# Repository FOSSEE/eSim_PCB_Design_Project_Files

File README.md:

# ESP32-Based Silent SOS and Emergency Alert System

## 1. Project Overview

The Silent SOS is an ESP32-based emergency alert system designed to help users send emergency notifications when they are in a potentially dangerous situation.

The system uses an MPU6050 motion sensor to detect abnormal movement. When a possible emergency is detected, the system provides a 5-second cancellation period. If the user does not cancel the alert, an emergency notification is triggered.

The project uses Wi-Fi connectivity to send alerts through Firebase and Telegram.

## 2. Project Objectives

- Design a compact PCB for the Silent SOS system.
- Interface the MPU6050 motion sensor with the ESP32.
- Detect potential emergency situations using motion data.
- Provide a 5-second cancellation period before sending an alert.
- Send emergency notifications using Wi-Fi connectivity.

## 3. Hardware Components

| Component | Purpose |
|---|---|
| ESP32 DevKit V1 | Main microcontroller |
| MPU6050 | Motion and orientation detection |
| BC547 transistor | Switching circuit |
| Supporting components | Circuit interfacing and protection |

## 4. System Working

The system operates in three different states:

1. **SAFE:** Normal operating condition.
2. **ARMED:** Emergency detection is enabled.
3. **DANGER:** A potential emergency is detected.

### Emergency Alert Process

1. The MPU6050 continuously provides motion data.
2. The ESP32 processes the sensor readings.
3. When a potential emergency is detected, the system enters the DANGER state.
4. A 5-second cancellation period is provided.
5. If the alert is not cancelled, an emergency notification is sent through Firebase and Telegram.
6. The user's location is obtained through the connected smartphone's GPS.

## 5. PCB Design

The PCB is designed using **KiCad**.

The design integrates the ESP32 interface, motion sensor connections, and supporting electronic circuitry into a compact board.

### PCB Design Files

| File | Description |
|---|---|
| `SOS.kicad_pro` | KiCad project file |
| `SOS.kicad_sch` | Circuit schematic |
| `SOS.kicad_pcb` | PCB layout |
| `SOS.proj` | Supporting project file |

## 6. Software and Tools

- KiCad – Schematic and PCB design
- Arduino IDE – ESP32 programming
- Firebase – Emergency alert integration
- Telegram Bot API – Emergency notifications

## 7. Applications

- Personal emergency assistance
- Women's safety applications
- Emergency notification systems
- Personal safety monitoring

## 8. Project Repository

This repository contains the PCB design files and supporting documentation developed for the eSim Semester Long Internship – Autumn 2026, Submission Task 7.

## 9. Author

**Kaushik N.**  
Department of Electronics and Communication Engineering  
Chennai Institute of Technology

---

**Project:** ESP32-Based Silent SOS and Emergency Alert System  
**Internship:** eSim Semester Long Internship – Autumn 2026

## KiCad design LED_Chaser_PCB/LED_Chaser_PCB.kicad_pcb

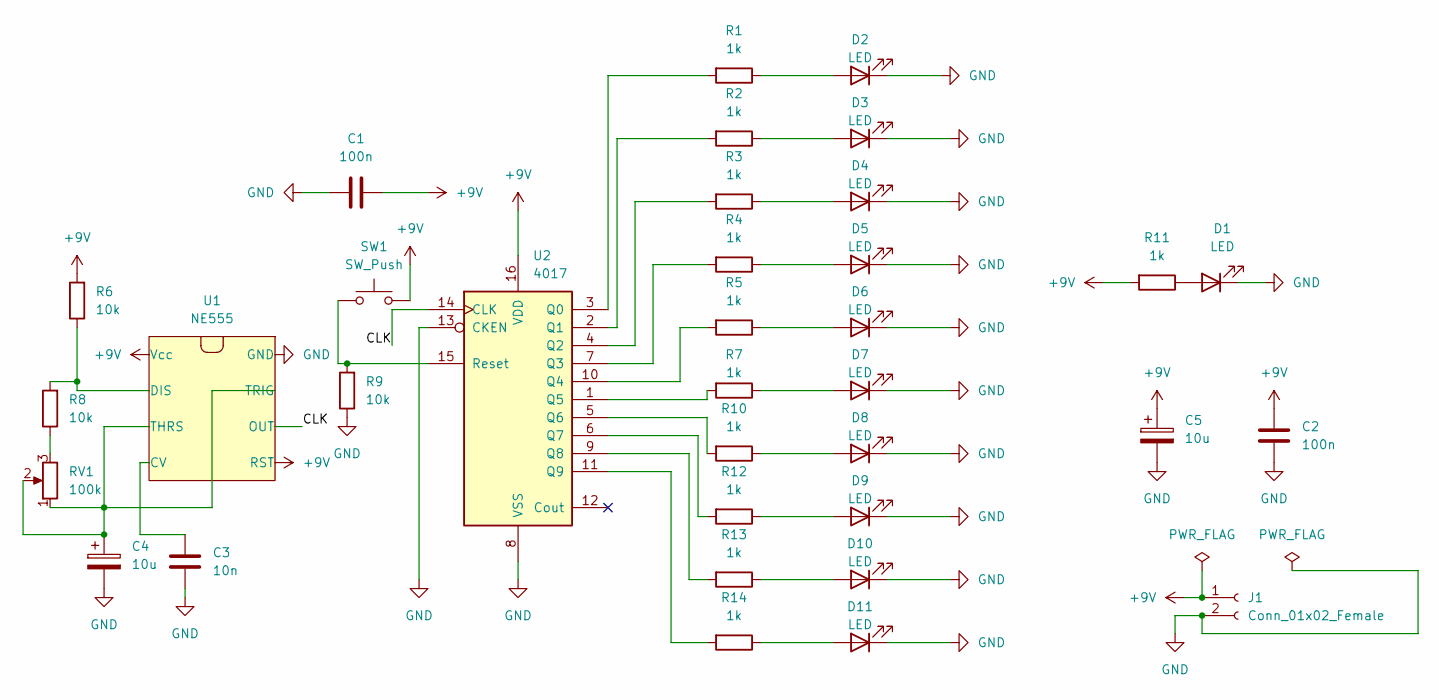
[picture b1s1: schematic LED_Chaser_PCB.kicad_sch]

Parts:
C1, C2: 100n; C_Disc_D5.0mm_W2.5mm_P5.00mm
C3: 10n; C_Disc_D5.0mm_W2.5mm_P5.00mm
C4, C5: 10u; CP_Radial_D5.0mm_P2.00mm
D1, D2, D3, D4, D5, D6, D7, D8, D9, D10, D11: LED; LED_D5.0mm
J1: Conn_01x02_Female; TerminalBlock_bornier-2_P5.08mm
R1, R2, R3, R4, R5, R7, R10, R11, R12, R13, R14: 1k; R_Axial_DIN0207_L6.3mm_D2.5mm_P7.62mm_Horizontal
R6, R8, R9: 10k; R_Axial_DIN0207_L6.3mm_D2.5mm_P7.62mm_Horizontal
RV1: 100k; Potentiometer_Alps_RK09K_Single_Vertical
SW1: SW_Push; SW_PUSH_6mm
U1: NE555; DIP-8_W7.62mm
U2: 4017; DIP-16_W7.62mm

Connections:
+9V: C1.1, C2.1, C5.1, J1.1, R6.2, R11.2, SW1.2, U1.4 (RST), U1.8 (Vcc), U2.16 (VDD)
/CLK: U1.3 (OUT), U2.14 (CLK)
GND: C1.2, C2.2, C3.2, C4.2, C5.2, D1.1 (K), D2.1 (K), D3.1 (K), D4.1 (K), D5.1 (K), D6.1 (K), D7.1 (K), D8.1 (K), D9.1 (K), D10.1 (K), D11.1 (K), J1.2, R9.1, U1.1 (GND), U2.8 (VSS), U2.13 (CKEN)
unnamed: D2.2 (A), R1.1
unnamed: D3.2 (A), R2.1
unnamed: D4.2 (A), R3.1
unnamed: D5.2 (A), R4.1
unnamed: D6.2 (A), R5.1
unnamed: R6.1, R8.2, U1.7 (DIS)
unnamed: D7.2 (A), R7.1
unnamed: R8.1, RV1.3
unnamed: D8.2 (A), R10.1
unnamed: D1.2 (A), R11.1
unnamed: D9.2 (A), R12.1
unnamed: D10.2 (A), R13.1
unnamed: D11.2 (A), R14.1
unnamed: R9.2, SW1.1, U2.15 (Reset)
unnamed: C4.1, RV1.1, RV1.2, U1.2 (TRIG), U1.6 (THRS)
unnamed: C3.1, U1.5 (CV)
unnamed: R7.2, U2.1 (Q5)
unnamed: R2.2, U2.2 (Q1)
unnamed: R1.2, U2.3 (Q0)
unnamed: R3.2, U2.4 (Q2)
unnamed: R10.2, U2.5 (Q6)
unnamed: R12.2, U2.6 (Q7)
unnamed: R4.2, U2.7 (Q3)
unnamed: R13.2, U2.9 (Q8)
unnamed: R5.2, U2.10 (Q4)
unnamed: R14.2, U2.11 (Q9)

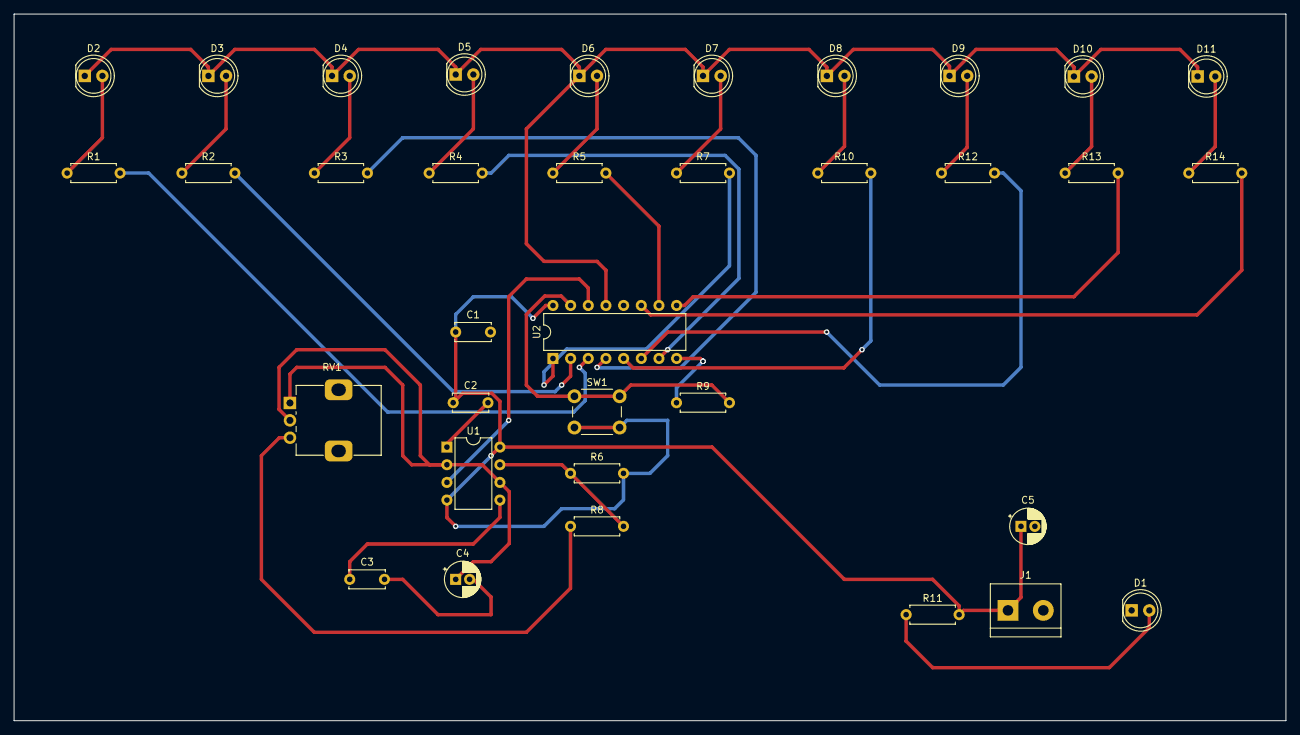
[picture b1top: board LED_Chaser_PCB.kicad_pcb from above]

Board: 2 copper layers, 182.9 x 101.6 mm, 35 parts (0 on the bottom side), 29 nets.

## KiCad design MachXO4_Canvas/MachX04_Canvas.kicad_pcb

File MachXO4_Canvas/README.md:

# MachXO4_Canvas — Custom 2-Layer Lattice MachXO4 FPGA Development Board

**IIT Bombay FOSSEE Winter Internship 2026 — Task 7: PCB Design using eSim (KiCad 9.0)**  
**Author:** Saurabh Sinha — Third-Year, B.Tech (Electronics & Communication Engineering), IIIT Naya Raipur  
**Verification Status:** `0 ERC Errors` • `0 DRC Errors` • `8 Hierarchical Schematic Sheets` • `100 × 100 mm 2-Layer PCB`

<p align="center">
  
  <br>
  <em>Figure 1: 3D rendered view of the MachXO4_Canvas development board showing the Lattice MachXO4-4300HC (TQFP-144), FTDI FT2232HL USB-JTAG/UART bridge, NCP1117 3.3 V LDO regulator, user LEDs, switches, and 4× bank expansion headers.</em>
</p>

> **5-Minute Technical Walkthrough & Hardware Demo:** [Watch Full Video Demonstration on Google Drive](https://drive.google.com/file/d/1bA2fzb_Q_-FsYkzUnRTprIzDjuLGJhoq/view?usp=sharing)  
> **Full Engineering Monograph (18 Pages):** [`MachXO4_Canvas_Task7_Report.pdf`](MachXO4_Canvas_Task7_Report.pdf)

---

## Why MachXO4_Canvas?

Most entry-level FPGA boards rely on external JTAG dongles, obscure fine-pitch BGAs, or opaque closed-source layouts. **MachXO4_Canvas** is a self-contained, open-source FPGA prototyping platform built entirely inside the **FOSSEE eSim / KiCad 9.0** workflow around the **Lattice MachXO4-4300HC (TQFP-144)**:

* **Single-Cable USB-JTAG & UART:** Integrated **FTDI FT2232HL** dual-channel bridge paired with a **93LC56C-I/SN** SPI configuration EEPROM—Channel A handles MPSSE JTAG bitstream programming while Channel B exposes a dedicated USB-UART telemetry port.
* **Per-Bank Power Integrity & Current Sensing:** Seven `1.0 Ω` series isolation resistors (`R40–R46`) feed `VCC_CORE` and `VCCIO0–VCCIO5` independently, damping simultaneous switching noise (SSN) and enabling non-invasive current profiling across individual I/O banks.
* **Hand-Solderable 2-Layer Architecture:** Engineered on a compact `100 × 100 mm` 2-layer stackup (`F.Cu` + `B.Cu` solid ground pours) using `0603` passives and gull-wing QFPs for straightforward lab assembly and probing.
* **Self-Contained Portable Libraries:** All 11 custom schematic symbols, SnapEDA footprints, and 3D STEP models resolve automatically via `${KIPRJMOD}` relative paths—zero manual library setup required.

---

## Hardware Architecture & Specifications

| Subsystem | Component / Parameter | Design Specification |
| :--- | :--- | :--- |
| **Core FPGA** | **Lattice MachXO4-4300HC** (`U4`) | TQFP-144 package, 4,300 LUTs, 6 independent I/O banks (`Bank 0–5`) |
| **USB-JTAG / UART** | **FTDI FT2232HL** (`U3`) + **93LC56C-I/SN** (`U2`) | Dual-channel Hi-Speed USB 2.0 bridge (Ch. A: JTAG, Ch. B: UART) |
| **Power Regulation** | **NCP1117ST33T3G** (`U1`) + `R40–R46` (`1.0 Ω`) | `+5 V` USB `VBUS` input → regulated `+3.3 V` core/I/O rails with distributed decoupling |
| **Clocking** | `Y1`, `Y2` | Dedicated on-board clock oscillator footprints feeding global clock pins |
| **User I/O & Debug** | `D1–D11`, `SW1–SW5` | 11 status/user LEDs, 4 tactile user pushbuttons, and 1 hardware reset (`4.7 kΩ / 0.1 µF` RC debounce) |
| **Expansion** | `J2–J5`, `J6` | 4× multi-bank GPIO pin headers + Type-A USB connector (`J6`) |
| **PCB Stackup & Rules** | 2-Layer (`F.Cu` / `B.Cu`) | `100 × 100 mm` outline, `0.2 mm` signal / `0.6 mm` power trace width, `0.9 / 0.5 mm` vias |
| **Verification** | KiCad 9.0 ERC & DRC | **0 Errors / 0 Unconnected Nets** (`ERC/ERC.rpt`, `ERC/DRC.rpt`) |

---

## Visual Design Gallery

| 2-Layer PCB Layout & Ground Pours | Hierarchical Root Schematic |
| :---: | :---: |
|  |  |
| *Routed `F.Cu` / `B.Cu` tracks (`0.2 mm` signal, `0.6 mm` power) with stitched ground planes.* | *8-sheet hierarchical architecture partitioning power, FT2232HL bridge, and FPGA banks.* |

---

## Quick Start in FOSSEE eSim / KiCad 9.0

1. **Clone or download** this repository (`machxo4-canvas-task7` branch).
2. Launch **FOSSEE eSim** (or **KiCad 9.0** directly) and open **`MachX04_Canvas/MachX04_Canvas.kicad_pro`**.
3. Open the **Schematic Editor**, **PCB Editor**, or **3D Viewer (`Alt+3`)**—all custom symbols (`local_symbols/`), footprints (`SnapEDA.pretty/`), and 3D STEP models (`local_3dmodels/`) load automatically via `${KIPRJMOD}`.

---

## Repository Structure

```text
MachX04_Canvas/
├── MachX04_Canvas.kicad_pro          # KiCad 9.0 project configuration
├── MachX04_Canvas.kicad_prl          # Project local settings
├── MachX04_Canvas.kicad_sch          # Hierarchical root schematic
├── MachX04_Canvas.kicad_pcb          # Routed 2-layer PCB layout (100 × 100 mm)
├── MachX04_Canvas.proj               # FOSSEE eSim project file
├── MachXO4_Canvas_Task7_Report.pdf   # 18-page technical design & verification report
├── sym-lib-table & fp-lib-table      # Portable ${KIPRJMOD} library tables
│
├── power_supply.kicad_sch            # Sub-sheet: +5 V USB VBUS to +3.3 V LDO regulator
├── ftdi_bridge.kicad_sch             # Sub-sheet: FT2232HL USB-JTAG/UART bridge & 93LC56C EEPROM
├── fpga_power.kicad_sch              # Sub-sheet: Core/bank power rails & 1.0 Ω isolation network
├── bank0.kicad_sch                   # Sub-sheet: FPGA Bank 0 I/O, LEDs & switches
├── bank1.kicad_sch                   # Sub-sheet: FPGA Bank 1 I/O, LEDs & header
├── bank2.kicad_sch                   # Sub-sheet: FPGA Bank 2 I/O, LEDs & header
├── bank345.kicad_sch                 # Sub-sheet: FPGA Banks 3/4/5 I/O, LEDs & headers
│
├── screenshots/                      # High-resolution 3D, PCB, and schematic renders
├── local_symbols/                    # 11 custom .kicad_sym symbol libraries
├── SnapEDA.pretty/                   # Custom SMD & THT footprints
├── local_3dmodels/                   # Custom 3D STEP component models
└── ERC/                              # Verified 0-error ERC.rpt and DRC.rpt logs
```

---

## References & Toolchain

* **EDA Suite:** [FOSSEE eSim](https://esim.fossee.in/) (KiCad 9.0.3)
* **FPGA Silicon:** [Lattice MachXO4 Family](https://www.latticesemi.com/Products/FPGAandCPLD/MachXO4) (`MachXO4-4300HC-5TG144C`)
* **USB Interface:** [FTDI FT2232HL Dual High-Speed USB to Multipurpose UART/FIFO IC](https://ftdichip.com/products/ft2232hl/)

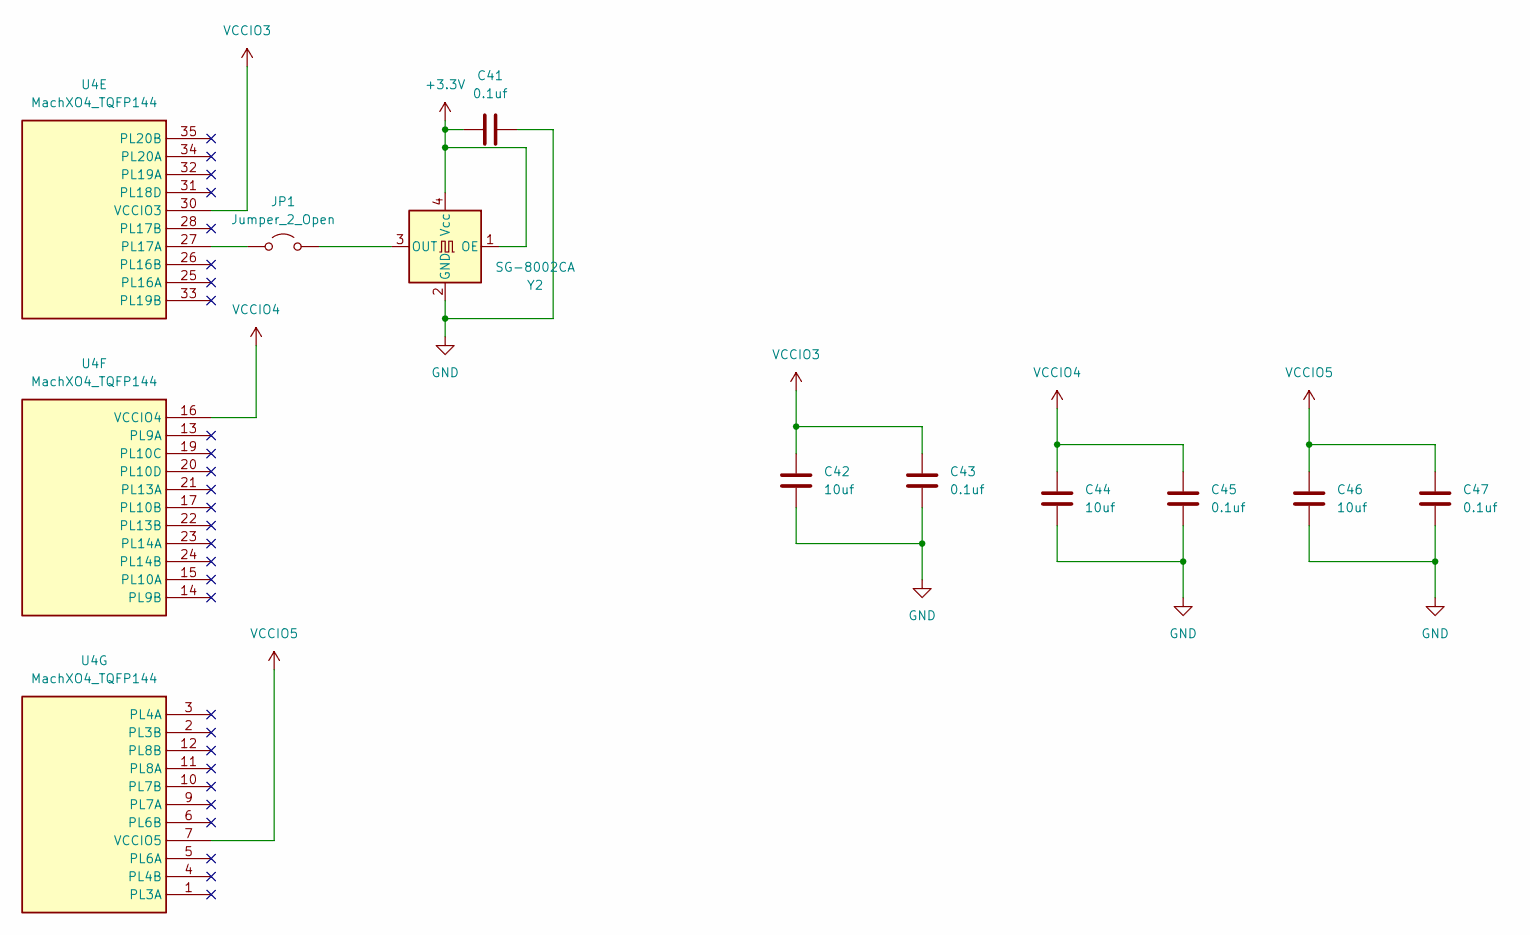
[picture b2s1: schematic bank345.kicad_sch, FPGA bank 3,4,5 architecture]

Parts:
C41, C43, C45, C47: 0.1uf; C_0603_1608Metric
C42, C44, C46: 10uf; C_0603_1608Metric
JP1: Jumper_2_Open; SolderJumper-2_P1.3mm_Bridged_RoundedPad1.0x1.5mm
U4: MachXO4_TQFP144; TQFP-144_20x20mm_P0.5mm
Y2: SG-8002CA; Oscillator_SMD_SeikoEpson_SG8002CA-4Pin_7.0x5.0mm

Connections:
+3.3V: C41.1, Y2.1 (OE), Y2.4 (Vcc); also elsewhere on the board
GND: C41.2, C42.1, C43.1, C44.1, C45.1, C46.1, C47.1, Y2.2 (GND); also elsewhere on the board
unnamed: JP1.1 (A), U4.27 (PL17A)
unnamed: JP1.2 (B), Y2.3 (OUT)
VCCIO3: C42.2, C43.2, U4.30 (VCCIO3); also elsewhere on the board
VCCIO4: C44.2, C45.2, U4.16 (VCCIO4); also elsewhere on the board
VCCIO5: C46.2, C47.2, U4.7 (VCCIO5); also elsewhere on the board

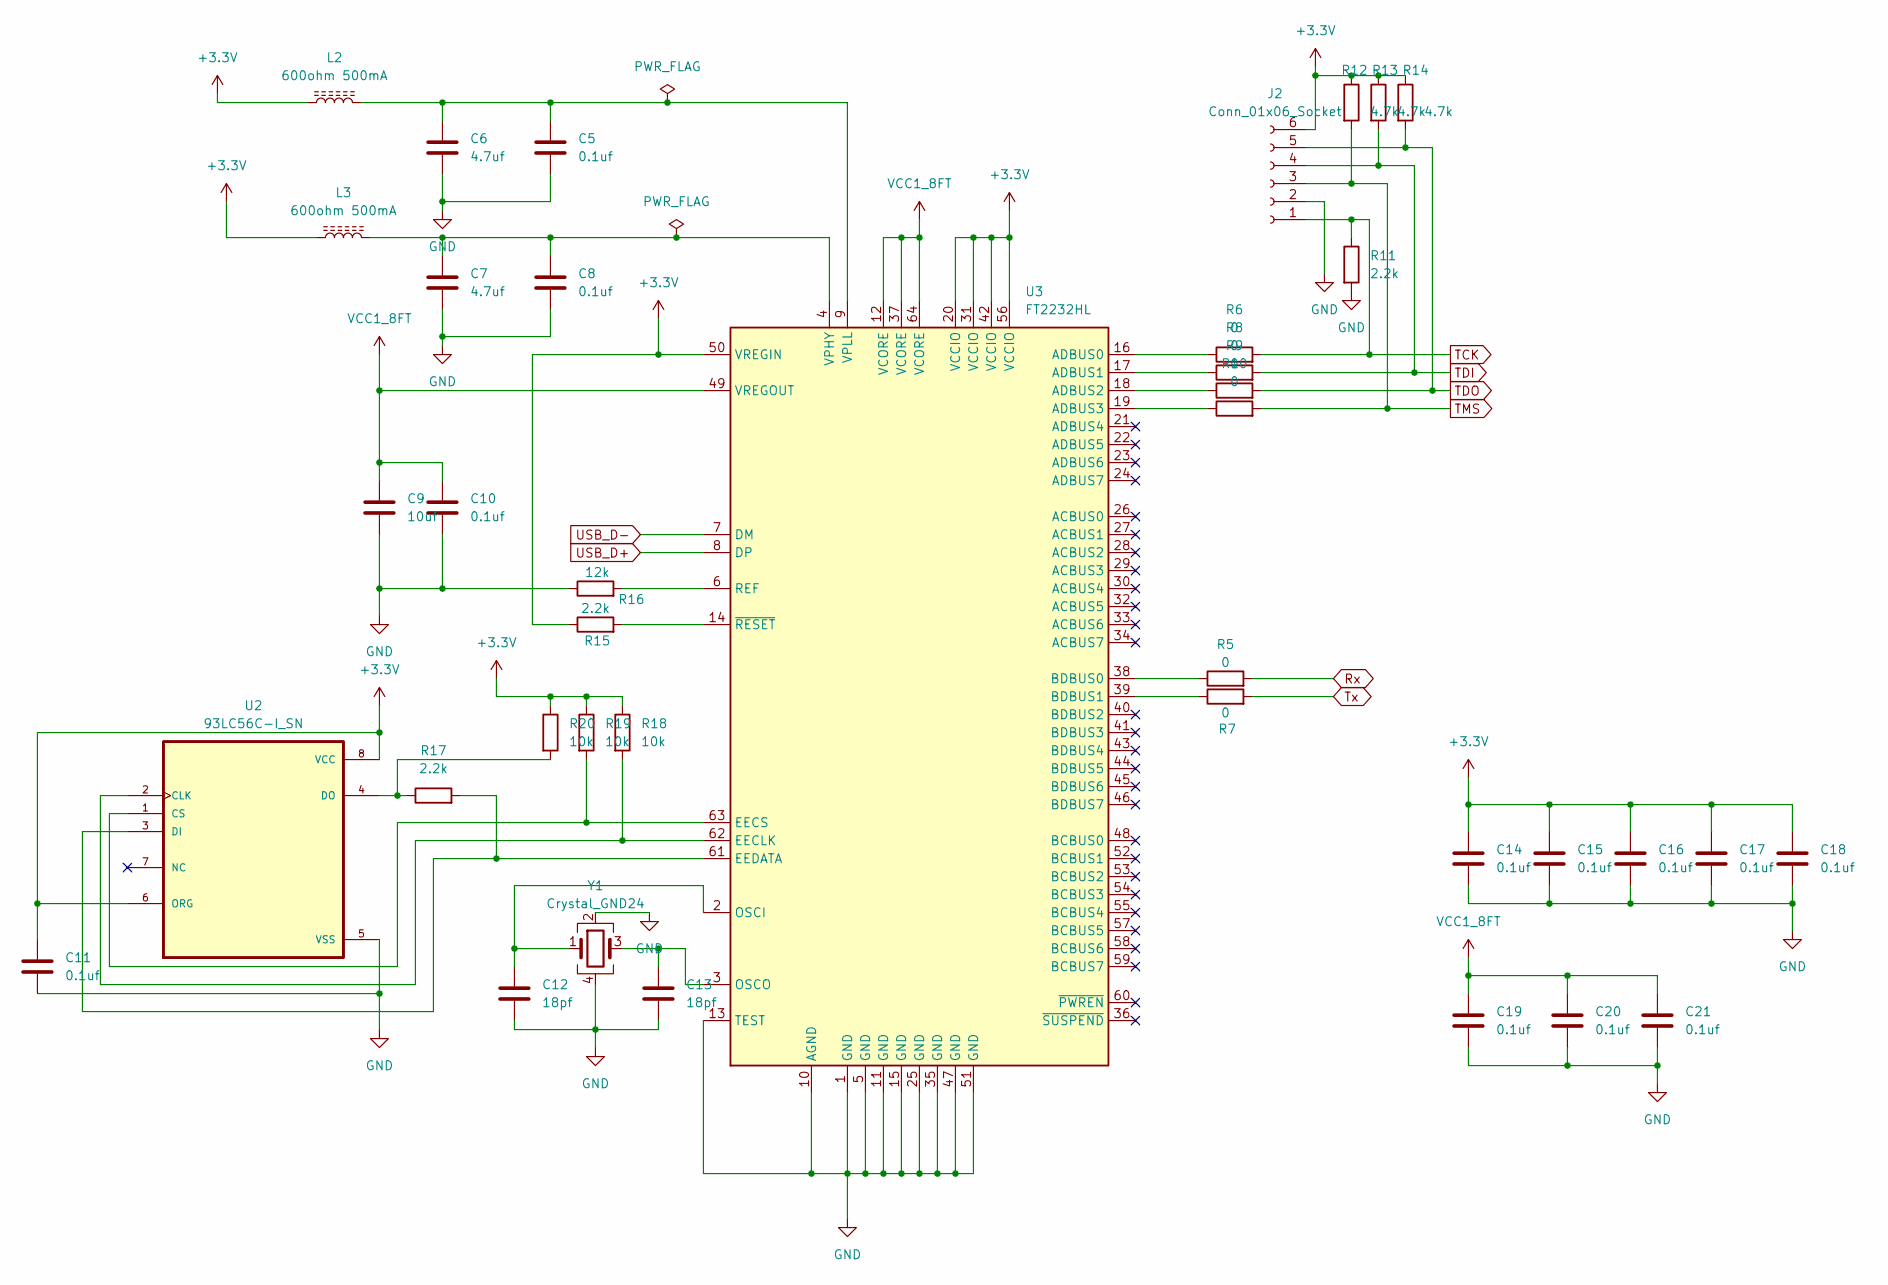
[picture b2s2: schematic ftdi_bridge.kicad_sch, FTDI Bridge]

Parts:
C5, C8, C10, C11, C14, C15, C16, C17, C18, C19, C20, C21: 0.1uf; C_0603_1608Metric
C6, C7: 4.7uf; C_0603_1608Metric
C9: 10uf; C_0603_1608Metric
C12, C13: 18pf; C_0603_1608Metric
J2: Conn_01x06_Socket; PinSocket_1x06_P2.54mm_Vertical
L2, L3: 600ohm 500mA; L_0603_1608Metric
R5, R6, R7, R8, R9, R10: 0; R_0603_1608Metric
R11, R15, R17: 2.2k; R_0603_1608Metric
R12, R13, R14: 4.7k; R_0603_1608Metric
R16: 12k; R_0603_1608Metric
R18, R19, R20: 10k; R_0603_1608Metric
U2: 93LC56C-I_SN; SOIC127P600X175-8N
U3: FT2232HL; LQFP-64_10x10mm_P0.5mm
Y1: Crystal_GND24; Crystal_SMD_3225-4Pin_3.2x2.5mm

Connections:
+3.3V: C11.1, C14.1, C15.1, C16.1, C17.1, C18.1, J2.6, L2.1, L3.1, R12.1, R13.1, R14.1, R15.1, R18.1, R19.1, R20.1, U2.6 (ORG), U2.8 (VCC), U3.20 (VCCIO), U3.31 (VCCIO), U3.42 (VCCIO), U3.50 (VREGIN), U3.56 (VCCIO); also elsewhere on the board
GND: C5.2, C6.2, C7.2, C8.2, C9.2, C10.2, C11.2, C12.2, C13.2, C14.2, C15.2, C16.2, C17.2, C18.2, C19.2, C20.2, C21.2, J2.2, R11.2, R16.1, U2.5 (VSS), U3.1 (GND), U3.5 (GND), U3.10 (AGND), U3.11 (GND), U3.13 (TEST), U3.15 (GND), U3.25 (GND), U3.35 (GND), U3.47 (GND), U3.51 (GND), Y1.2 (G), Y1.4 (G); also elsewhere on the board
unnamed: R18.2, U2.2 (CLK), U3.62 (EECLK)
unnamed: R19.2, U2.1 (CS), U3.63 (EECS)
unnamed: R17.2, U2.3 (DI), U3.61 (EEDATA)
unnamed: R17.1, R20.2, U2.4 (DO)
unnamed: R6.1, U3.16 (ADBUS0)
unnamed: R8.1, U3.17 (ADBUS1)
unnamed: R9.1, U3.18 (ADBUS2)
unnamed: R10.1, U3.19 (ADBUS3)
unnamed: R5.1, U3.38 (BDBUS0)
unnamed: R7.1, U3.39 (BDBUS1)
unnamed: C12.1, U3.2 (OSCI), Y1.1
unnamed: C13.1, U3.3 (OSCO), Y1.3
unnamed: R16.2, U3.6 (REF)
unnamed: C7.1, C8.1, L3.2, U3.4 (VPHY)
unnamed: C5.1, C6.1, L2.2, U3.9 (VPLL)
unnamed: R15.2, U3.14 (~RESET)
Rx: R5.2; also elsewhere on the board
TCK: J2.1, R6.2, R11.1; also elsewhere on the board
TDI: J2.4, R8.2, R13.2; also elsewhere on the board
TDO: J2.5, R9.2, R14.2; also elsewhere on the board
TMS: J2.3, R10.2, R12.2; also elsewhere on the board
Tx: R7.2; also elsewhere on the board
USB_D+: U3.8 (DP); also elsewhere on the board
USB_D-: U3.7 (DM); also elsewhere on the board
VCC1_8FT: C9.1, C10.1, C19.1, C20.1, C21.1, U3.12 (VCORE), U3.37 (VCORE), U3.49 (VREGOUT), U3.64 (VCORE)

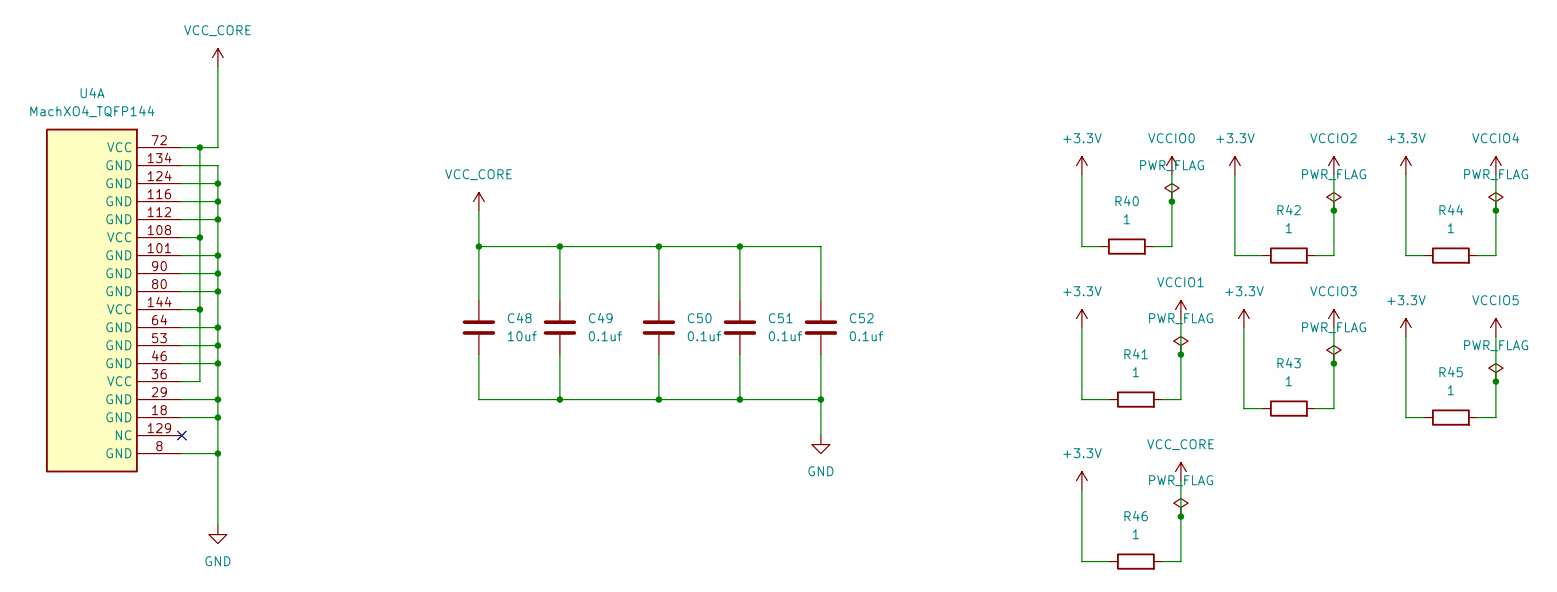
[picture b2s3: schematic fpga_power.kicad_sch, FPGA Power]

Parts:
C48: 10uf; C_0603_1608Metric
C49, C50, C51, C52: 0.1uf; C_0603_1608Metric
R40, R41, R42, R43, R44, R45, R46: 1; R_0603_1608Metric
U4: MachXO4_TQFP144; TQFP-144_20x20mm_P0.5mm

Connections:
+3.3V: R40.1, R41.1, R42.1, R43.1, R44.1, R45.1, R46.1; also elsewhere on the board
GND: C48.2, C49.2, C50.2, C51.2, C52.2, U4.8 (GND), U4.18 (GND), U4.29 (GND), U4.46 (GND), U4.53 (GND), U4.64 (GND), U4.80 (GND), U4.90 (GND), U4.101 (GND), U4.112 (GND), U4.116 (GND), U4.124 (GND), U4.134 (GND); also elsewhere on the board
VCCIO0: R40.2; also elsewhere on the board
VCCIO1: R41.2; also elsewhere on the board
VCCIO2: R42.2; also elsewhere on the board
VCCIO3: R43.2; also elsewhere on the board
VCCIO4: R44.2; also elsewhere on the board
VCCIO5: R45.2; also elsewhere on the board
VCC_CORE: C48.1, C49.1, C50.1, C51.1, C52.1, R46.2, U4.36 (VCC), U4.72 (VCC), U4.108 (VCC), U4.144 (VCC)

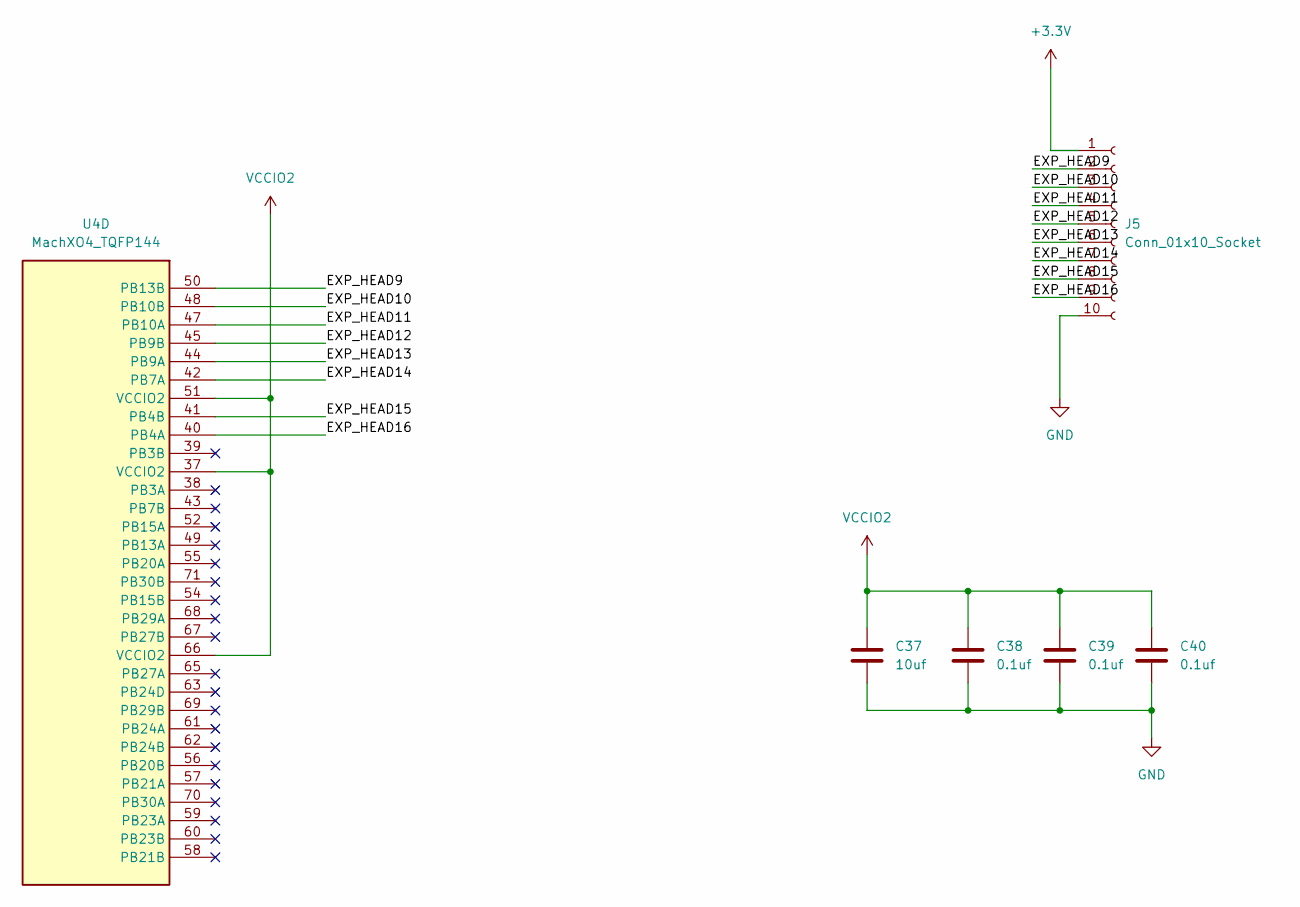
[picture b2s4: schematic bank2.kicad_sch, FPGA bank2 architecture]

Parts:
C37: 10uf; C_0603_1608Metric
C38, C39, C40: 0.1uf; C_0603_1608Metric
J5: Conn_01x10_Socket; PinHeader_1x10_P2.54mm_Vertical
U4: MachXO4_TQFP144; TQFP-144_20x20mm_P0.5mm

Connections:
+3.3V: J5.1; also elsewhere on the board
/bank2/EXP_HEAD9: J5.2, U4.50 (PB13B)
/bank2/EXP_HEAD10: J5.3, U4.48 (PB10B)
/bank2/EXP_HEAD11: J5.4, U4.47 (PB10A)
/bank2/EXP_HEAD12: J5.5, U4.45 (PB9B)
/bank2/EXP_HEAD13: J5.6, U4.44 (PB9A)
/bank2/EXP_HEAD14: J5.7, U4.42 (PB7A)
/bank2/EXP_HEAD15: J5.8, U4.41 (PB4B)
/bank2/EXP_HEAD16: J5.9, U4.40 (PB4A)
GND: C37.2, C38.2, C39.2, C40.2, J5.10; also elsewhere on the board
VCCIO2: C37.1, C38.1, C39.1, C40.1, U4.37 (VCCIO2), U4.51 (VCCIO2), U4.66 (VCCIO2); also elsewhere on the board

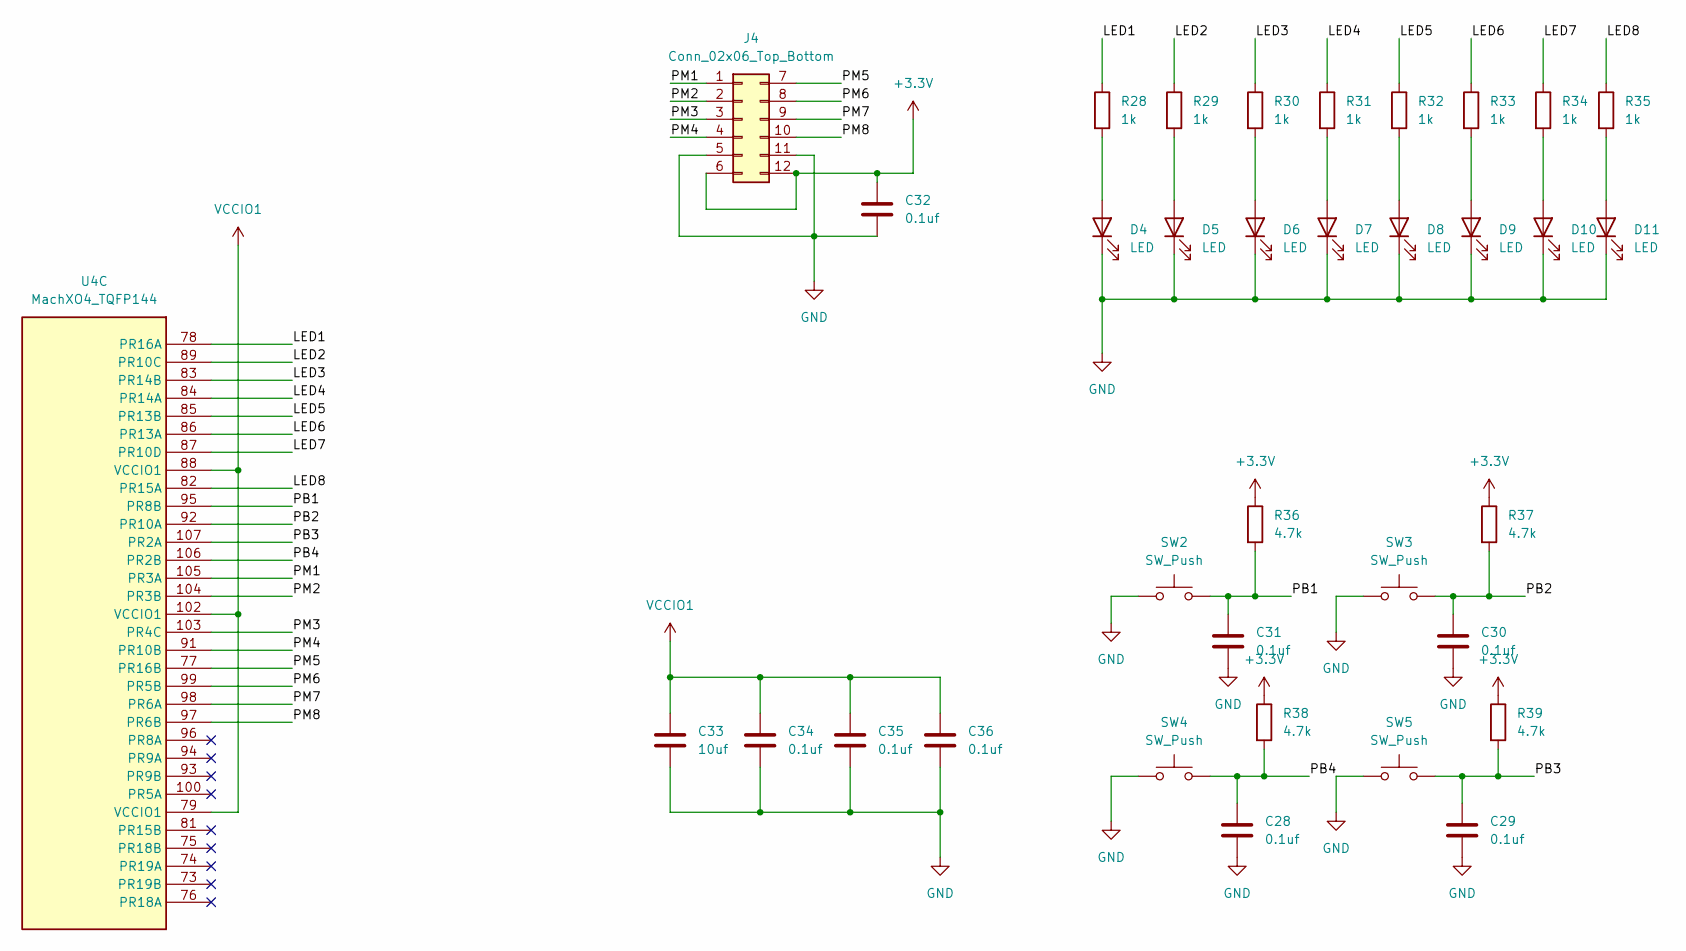
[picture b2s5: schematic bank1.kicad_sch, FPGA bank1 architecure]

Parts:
C28, C29, C30, C31, C32, C34, C35, C36: 0.1uf; C_0603_1608Metric
C33: 10uf; C_0603_1608Metric
D4, D5, D6, D7, D8, D9, D10, D11: LED; LED_0603_1608Metric
J4: Conn_02x06_Top_Bottom; PinSocket_2x06_P2.54mm_Vertical
R28, R29, R30, R31, R32, R33, R34, R35: 1k; R_0603_1608Metric
R36, R37, R38, R39: 4.7k; R_0603_1608Metric
SW2, SW3, SW4, SW5: SW_Push; SW_SPST_B3U-1000P
U4: MachXO4_TQFP144; TQFP-144_20x20mm_P0.5mm

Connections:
+3.3V: C32.1, J4.6, J4.12, R36.1, R37.1, R38.1, R39.1; also elsewhere on the board
/bank1/LED1: R28.1, U4.78 (PR16A)
/bank1/LED2: R29.1, U4.89 (PR10C)
/bank1/LED3: R30.1, U4.83 (PR14B)
/bank1/LED4: R31.1, U4.84 (PR14A)
/bank1/LED5: R32.1, U4.85 (PR13B)
/bank1/LED6: R33.1, U4.86 (PR13A)
/bank1/LED7: R34.1, U4.87 (PR10D)
/bank1/LED8: R35.1, U4.82 (PR15A)
/bank1/PB1: C31.1, R36.2, SW2.2, U4.95 (PR8B)
/bank1/PB2: C30.1, R37.2, SW3.2, U4.92 (PR10A)
/bank1/PB3: C29.1, R39.2, SW5.2, U4.107 (PR2A)
/bank1/PB4: C28.1, R38.2, SW4.2, U4.106 (PR2B)
/bank1/PM1: J4.1, U4.105 (PR3A)
/bank1/PM2: J4.2, U4.104 (PR3B)
/bank1/PM3: J4.3, U4.103 (PR4C)
/bank1/PM4: J4.4, U4.91 (PR10B)
/bank1/PM5: J4.7, U4.77 (PR16B)
/bank1/PM6: J4.8, U4.99 (PR5B)
/bank1/PM7: J4.9, U4.98 (PR6A)
/bank1/PM8: J4.10, U4.97 (PR6B)
GND: C28.2, C29.2, C30.2, C31.2, C32.2, C33.2, C34.2, C35.2, C36.2, D4.1 (K), D5.1 (K), D6.1 (K), D7.1 (K), D8.1 (K), D9.1 (K), D10.1 (K), D11.1 (K), J4.5, J4.11, SW2.1, SW3.1, SW4.1, SW5.1; also elsewhere on the board
unnamed: D4.2 (A), R28.2
unnamed: D5.2 (A), R29.2
unnamed: D6.2 (A), R30.2
unnamed: D7.2 (A), R31.2
unnamed: D8.2 (A), R32.2
unnamed: D9.2 (A), R33.2
unnamed: D10.2 (A), R34.2
unnamed: D11.2 (A), R35.2
VCCIO1: C33.1, C34.1, C35.1, C36.1, U4.79 (VCCIO1), U4.88 (VCCIO1), U4.102 (VCCIO1); also elsewhere on the board

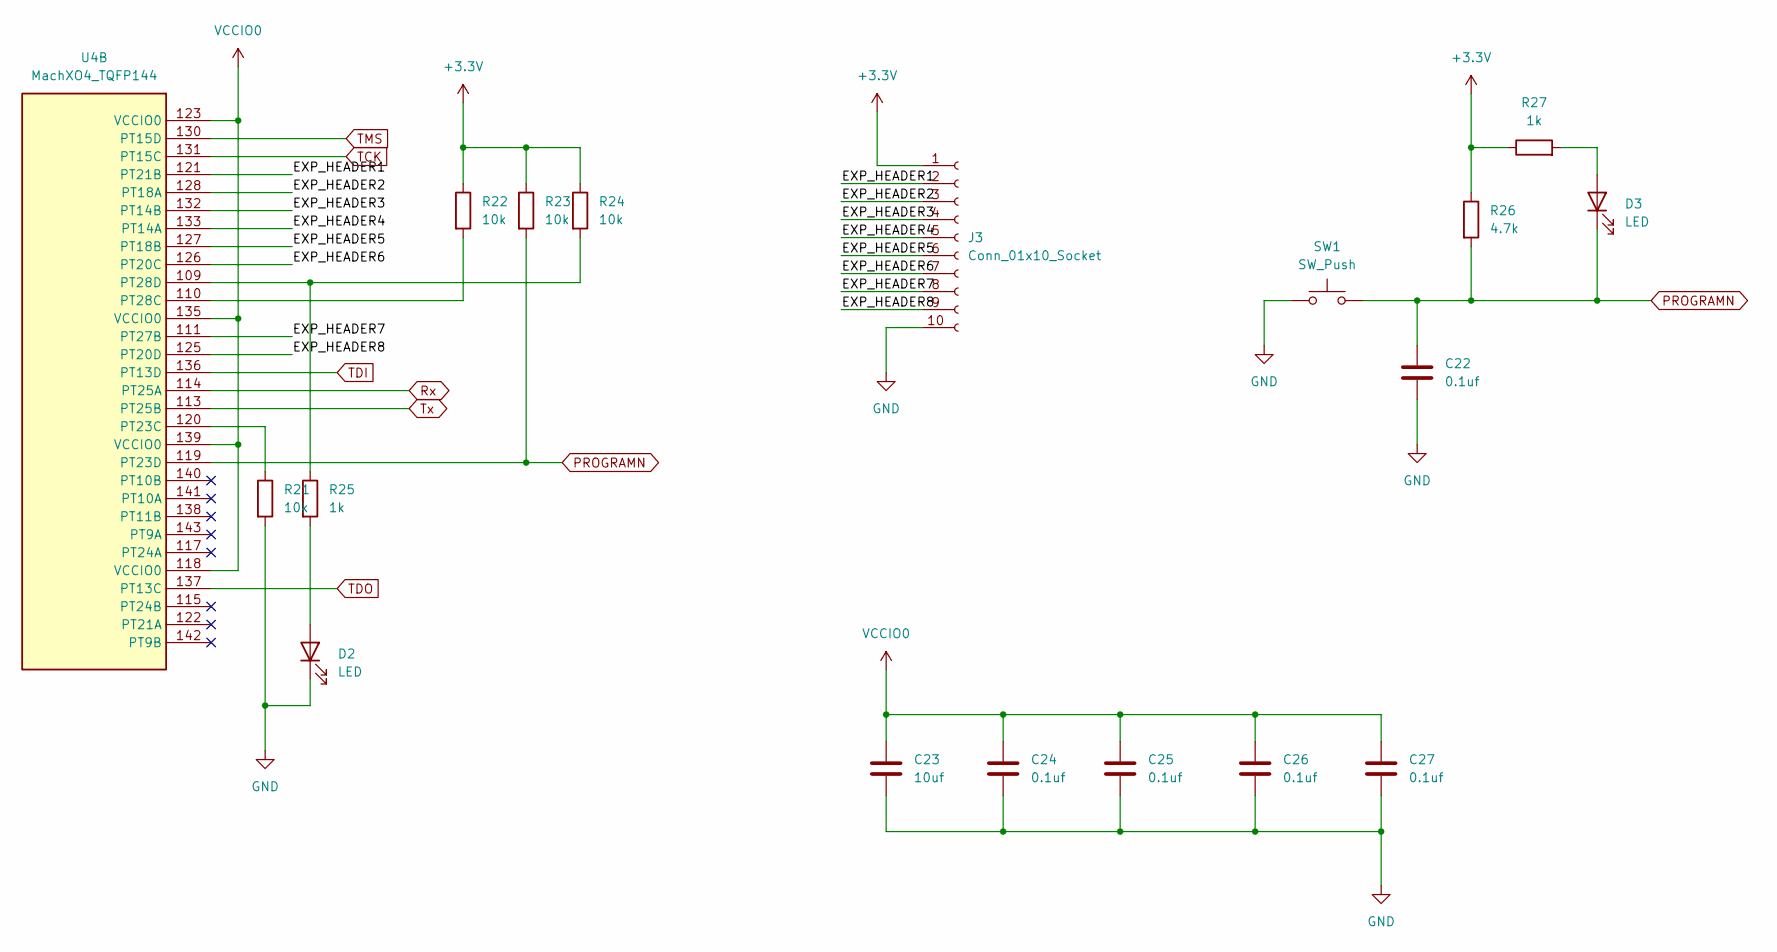
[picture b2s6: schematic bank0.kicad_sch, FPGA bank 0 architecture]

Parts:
C22, C24, C25, C26, C27: 0.1uf; C_0603_1608Metric
C23: 10uf; C_0603_1608Metric
D2, D3: LED; LED_0603_1608Metric
J3: Conn_01x10_Socket; PinHeader_1x10_P2.54mm_Vertical
R21, R22, R23, R24: 10k; R_0603_1608Metric
R25, R27: 1k; R_0603_1608Metric
R26: 4.7k; R_0603_1608Metric
SW1: SW_Push; SW_SPST_B3U-1000P
U4: MachXO4_TQFP144; TQFP-144_20x20mm_P0.5mm

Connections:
+3.3V: J3.1, R22.1, R23.1, R24.1, R26.1, R27.1; also elsewhere on the board
/bank0/EXP_HEADER1: J3.2, U4.121 (PT21B)
/bank0/EXP_HEADER2: J3.3, U4.128 (PT18A)
/bank0/EXP_HEADER3: J3.4, U4.132 (PT14B)
/bank0/EXP_HEADER4: J3.5, U4.133 (PT14A)
/bank0/EXP_HEADER5: J3.6, U4.127 (PT18B)
/bank0/EXP_HEADER6: J3.7, U4.126 (PT20C)
/bank0/EXP_HEADER7: J3.8, U4.111 (PT27B)
/bank0/EXP_HEADER8: J3.9, U4.125 (PT20D)
GND: C22.2, C23.2, C24.2, C25.2, C26.2, C27.2, D2.1 (K), J3.10, R21.2, SW1.1; also elsewhere on the board
unnamed: D2.2 (A), R25.2
unnamed: D3.2 (A), R27.2
unnamed: R21.1, U4.120 (PT23C)
unnamed: R22.2, U4.110 (PT28C)
unnamed: R24.2, R25.1, U4.109 (PT28D)
PROGRAMN: C22.1, D3.1 (K), R23.2, R26.2, SW1.2, U4.119 (PT23D)
Rx: U4.114 (PT25A); also elsewhere on the board
TCK: U4.131 (PT15C); also elsewhere on the board
TDI: U4.136 (PT13D); also elsewhere on the board
TDO: U4.137 (PT13C); also elsewhere on the board
TMS: U4.130 (PT15D); also elsewhere on the board
Tx: U4.113 (PT25B); also elsewhere on the board
VCCIO0: C23.1, C24.1, C25.1, C26.1, C27.1, U4.118 (VCCIO0), U4.123 (VCCIO0), U4.135 (VCCIO0), U4.139 (VCCIO0); also elsewhere on the board

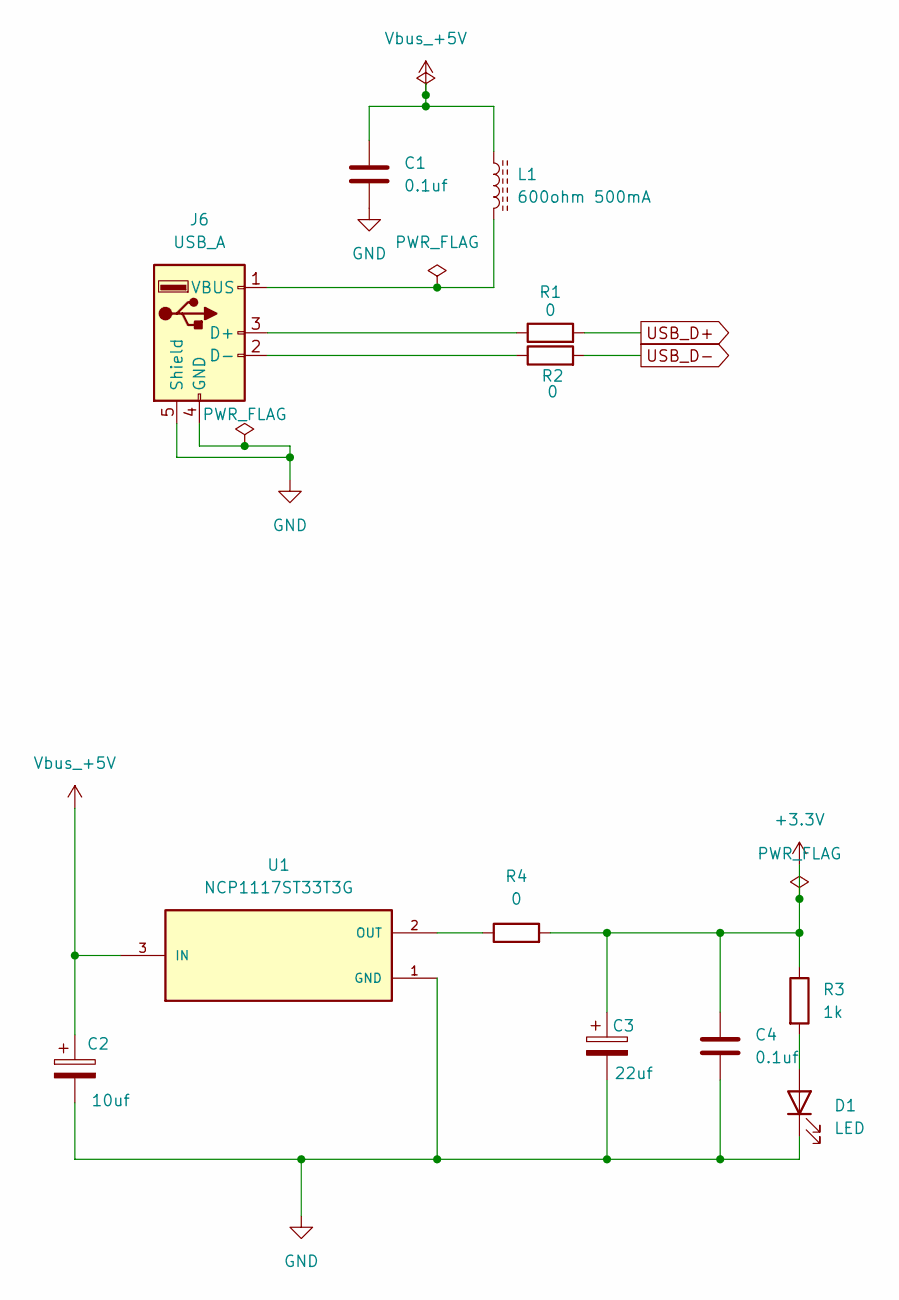
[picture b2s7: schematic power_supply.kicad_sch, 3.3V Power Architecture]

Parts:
C1, C4: 0.1uf; C_0603_1608Metric
C2: 10uf; C_0603_1608Metric
C3: 22uf; C_0603_1608Metric
D1: LED; LED_0603_1608Metric
J6: USB_A; 61400416021
L1: 600ohm 500mA; L_0603_1608Metric
R1, R2, R4: 0; R_0603_1608Metric
R3: 1k; R_0603_1608Metric
U1: NCP1117ST33T3G; SOT230P700X180-4N

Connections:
+3.3V: C3.1, C4.1, R3.1, R4.2; also elsewhere on the board
GND: C1.2, C2.2, C3.2, C4.2, D1.1 (K), J6.4 (GND), J6.5 (Shield), U1.1 (GND); also elsewhere on the board
unnamed: D1.2 (A), R3.2
unnamed: J6.3 (D+), R1.1
unnamed: J6.2 (D-), R2.1
unnamed: J6.1 (VBUS), L1.2
unnamed: R4.1, U1.2 (OUT), U1.4 (OUT)
USB_D+: R1.2; also elsewhere on the board
USB_D-: R2.2; also elsewhere on the board
Vbus_+5V: C1.1, C2.1, L1.1, U1.3 (IN)
